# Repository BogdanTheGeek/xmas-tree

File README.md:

# Christmas Tree RGB Bauble
A while ago I ordered a rell of 1k 1.2x1.2mm RGB LEDs for $0.002 each and I wanted to use them for something.
The circuit has provisions for a very small SEPIC converter that could be used as a constant current charging source for a built in battery.

I didn't get a chance to port my code from [my cheap power supply project](https://github.com/BogdanTheGeek/CCCCPPPS), but the bauble ended up very nice.

This was my first time programming charlieplexed animations so the code may not be efficient, but it's quite nice to work with I think.

This design was optimised solely to be easy to make on my CNC mill and etch with my home setup, which is why it's in a frame.

# Demo
[video](https://github.com/user-attachments/assets/888284c0-78c8-478a-b54b-9dfa2ae81bd1)

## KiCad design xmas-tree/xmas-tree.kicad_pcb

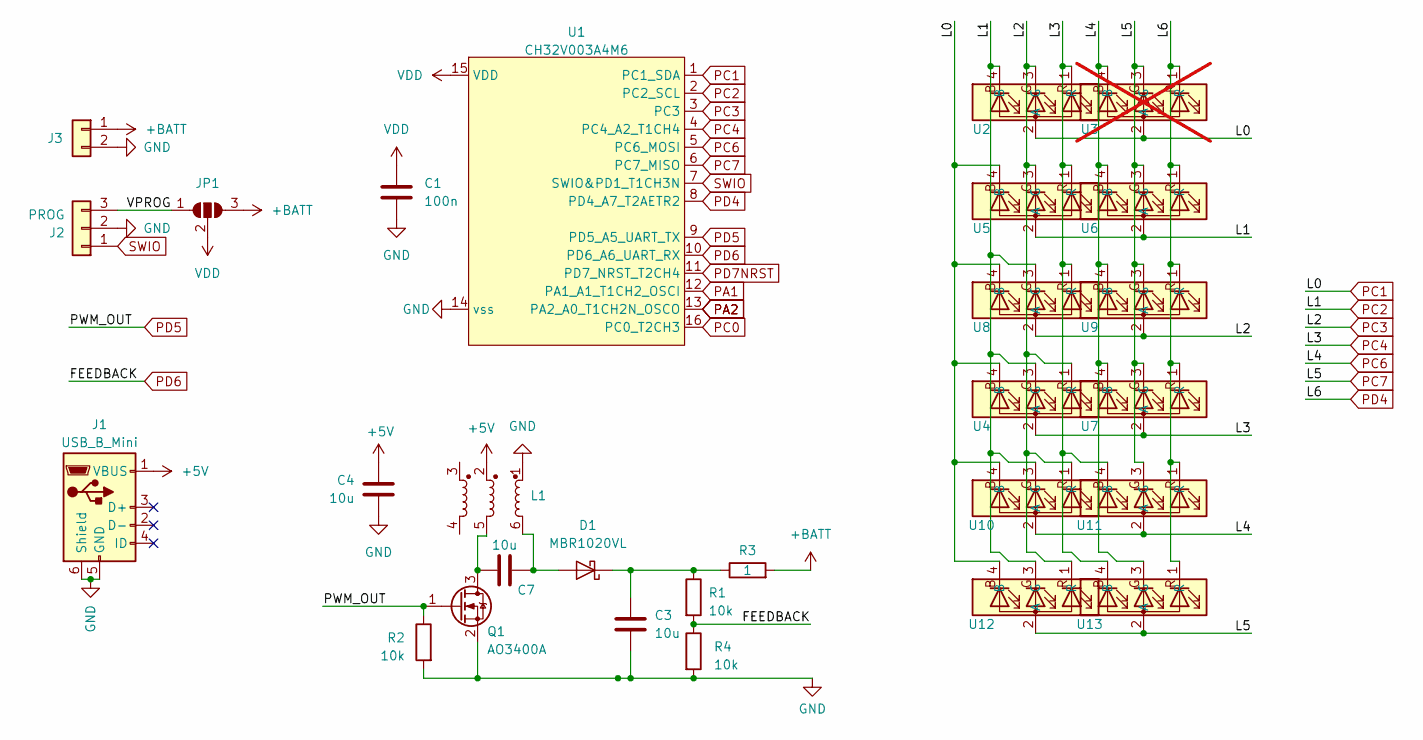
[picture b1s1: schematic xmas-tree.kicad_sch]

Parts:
C1: 100n; C_0603_1608Metric_Pad1.08x0.95mm_HandSolder
C3, C4, C7: 10u; C_0603_1608Metric_Pad1.08x0.95mm_HandSolder
D1: MBR1020VL; D_SOD-123F
J1: USB_B_Mini; USB_Mini-B_Lumberg_2486_01_Horizontal
J2: PROG; PinHeader_1x03_P2.54mm_Vertical
J3: Conn_01x02; PinSocket_1x02_P2.54mm_Vertical
JP1: SolderJumper_3_Open; SolderJumper-3_P1.3mm_Open_RoundedPad1.0x1.5mm
L1: CM3225T-801; L_CommonModeChoke_TDK_ACM2520-3P
Q1: AO3400A; SOT-23
R1, R2, R4: 10k; R_0603_1608Metric_Pad0.98x0.95mm_HandSolder
R3: 1; R_1210_3225Metric_Pad1.30x2.65mm_HandSolder
U1: CH32V003A4M6; SO-16_3.9x9.9mm_P1.27mm
U2, U4, U5, U6, U7, U8, U9, U10, U11, U12, U13: XL-B1212RGBA-HF; LED-SMD_4P-L1.2-W1.2_BR; LCSC Part C22461780
U3: XL-B1212RGBA-HF; LED-SMD_4P-L1.2-W1.2_BR; LCSC Part C22461780; not fitted

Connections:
+5V: C4.1, J1.1 (VBUS), L1.2
+BATT: J3.1, JP1.3 (B), R3.2
/VPROG: J2.3, JP1.1 (A)
GND: C1.2, C3.2, C4.2, J1.5 (GND), J1.6 (Shield), J2.2, J3.2, L1.1, Q1.2 (S), R2.2, R4.2, U1.14 (vss)
unnamed: C7.2, D1.2 (A), L1.6
unnamed: C3.1, D1.1 (K), R1.1, R3.1
unnamed: C7.1, L1.5, Q1.3 (D)
PA1: U1.12 (PA1_A1_T1CH2_OSCI)
PA2: U1.13 (PA2_A0_T1CH2N_OSCO)
PC0: U1.16 (PC0_T2CH3)
PC1: U1.1 (PC1_SDA), U2.2 (A), U3.2 (A), U4.4 (B), U5.4 (B), U8.4 (B), U10.4 (B), U12.4 (B)
PC2: U1.2 (PC2_SCL), U2.4 (B), U4.3 (G), U5.2 (A), U6.2 (A), U8.3 (G), U10.3 (G), U12.3 (G)
PC3: U1.3 (PC3), U2.3 (G), U4.1 (R), U5.3 (G), U8.2 (A), U9.2 (A), U10.1 (R), U12.1 (R)
PC4: U1.4 (PC4_A2_T1CH4), U2.1 (R), U4.2 (A), U5.1 (R), U7.2 (A), U8.1 (R), U11.4 (B), U13.4 (B)
PC6: U1.5 (PC6_MOSI), U3.4 (B), U6.4 (B), U7.4 (B), U9.4 (B), U10.2 (A), U11.2 (A), U13.3 (G)
PC7: U1.6 (PC7_MISO), U3.3 (G), U6.3 (G), U7.3 (G), U9.3 (G), U11.3 (G), U12.2 (A), U13.2 (A)
PD4: U1.8 (PD4_A7_T2AETR2), U3.1 (R), U6.1 (R), U7.1 (R), U9.1 (R), U11.1 (R), U13.1 (R)
PD5: Q1.1 (G), R2.1, U1.9 (PD5_A5_UART_TX)
PD6: R1.2, R4.1, U1.10 (PD6_A6_UART_RX)
PD7NRST: U1.11 (PD7_NRST_T2CH4)
SWIO: J2.1, U1.7 (SWIO&PD1_T1CH3N)
VDD: C1.1, JP1.2 (C), U1.15 (VDD)

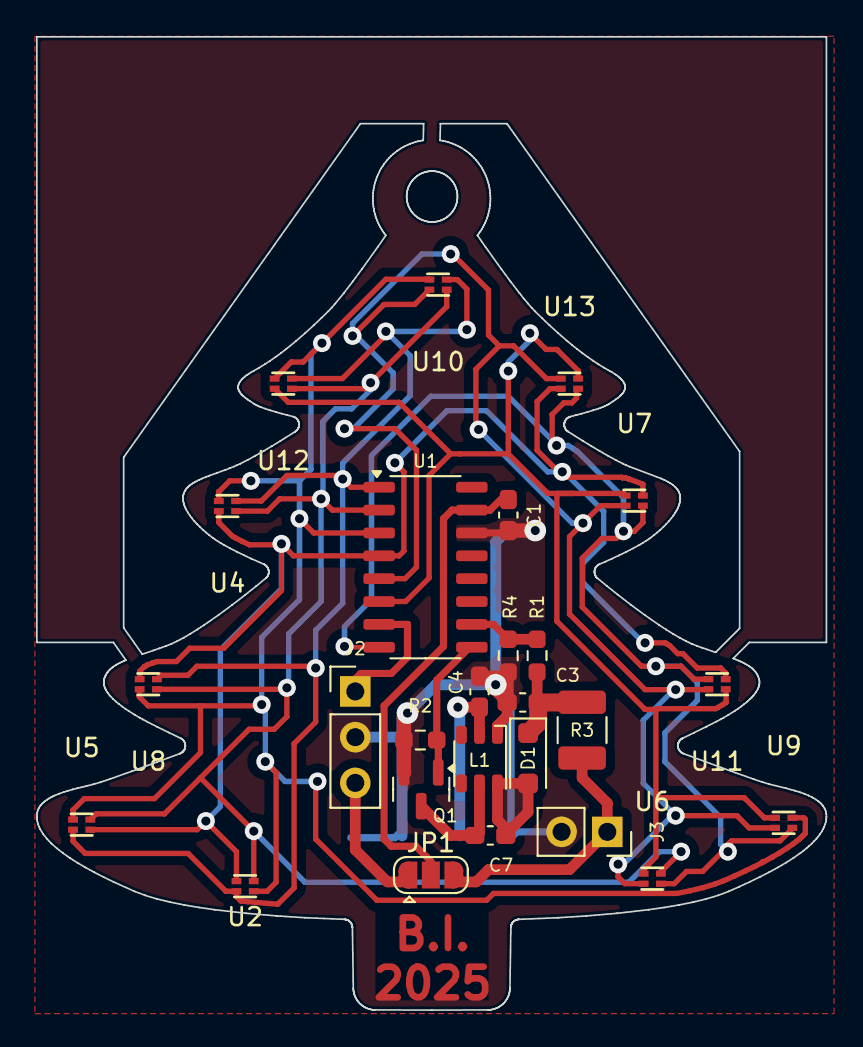
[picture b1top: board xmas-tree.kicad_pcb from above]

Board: 2 copper layers, 43.9 x 54.1 mm, 27 parts (1 on the bottom side), 18 nets.

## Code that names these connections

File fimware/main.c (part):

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#define Rin 100
#define Rt ( Rf + Rin )

#define L0 PC1
#define L1 PC2
#define L2 PC3
#define L3 PC4
#define L4 PC6
#define L5 PC7
#define L6 PD4

uint8_t pins[] = { L0, L1, L2, L3, L4, L5, L6 };

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	// Configure ADC.
	RCC->APB2PCENR |= RCC_APB2Periph_GPIOD | RCC_APB2Periph_ADC1;

	// PD6 is analog input ch 6
	GPIOD->CFGLR &= ~( 0xf << ( 6 << 2 ) ); // CNF = 00: Analog, MODE = 00: Input

	// Reset the ADC to init all regs
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
	AFIO->PCFR1 |= GPIO_FullRemap_TIM2;

	// PD5 is T2CH4
	funPinMode( PD5, ( GPIO_Speed_10MHz | GPIO_CNF_OUT_PP_AF ) );

	// Reset TIM2 to init all regs
	RCC->APB1PRSTR |= RCC_APB1Periph_TIM2;
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
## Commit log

2026-01-02 init
2026-01-02 Add MIT License to the project
2026-01-02 Add project details
